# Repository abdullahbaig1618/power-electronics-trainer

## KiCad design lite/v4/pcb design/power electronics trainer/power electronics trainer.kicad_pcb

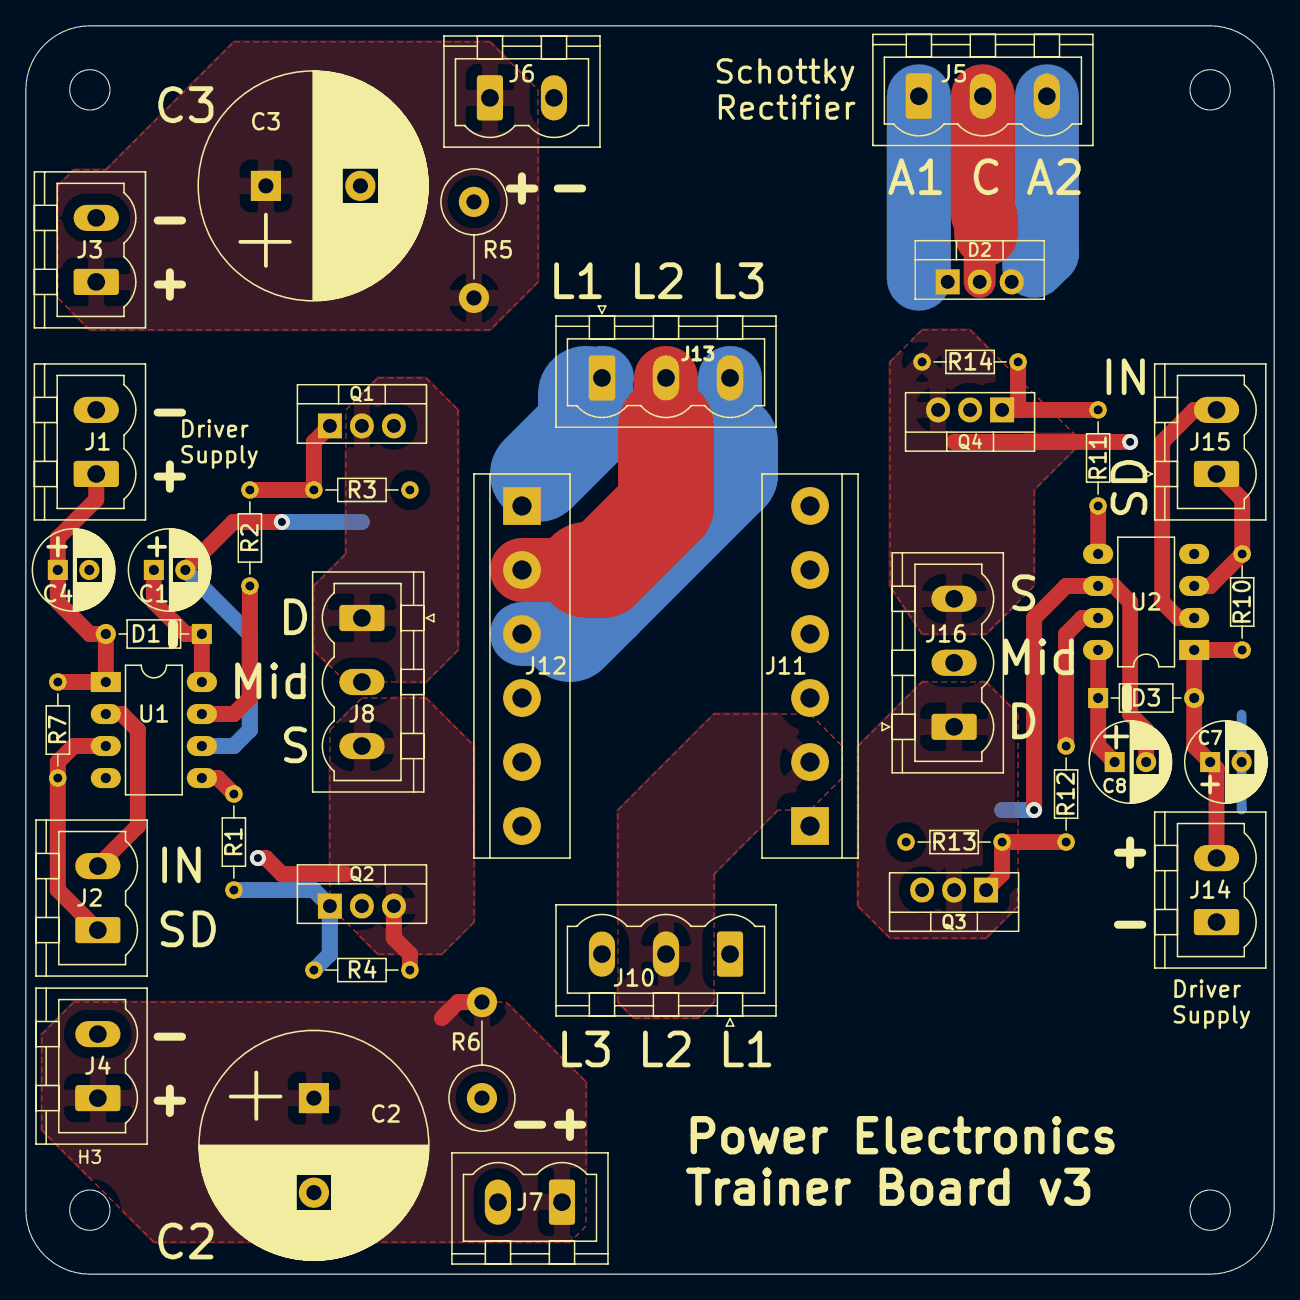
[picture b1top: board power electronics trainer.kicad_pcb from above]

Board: 2 copper layers, 99.1 x 99.1 mm, 46 parts (0 on the bottom side), 35 nets.

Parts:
C1, C4, C7, C8: 10uF; CP_Radial_D6.3mm_P2.50mm
C2, C3: 1000uF; CP_Radial_D18.0mm_P7.50mm
D1, D3: 1N4148; D_DO-35_SOD27_P7.62mm_Horizontal
D2: MBR20100CT; TO-220-3_Vertical
H1, H2, H3, H4: MountingHole; MountingHole_3.2mm_M3
J1, J2, J3, J4, J6, J7, J14, J15: Screw_Terminal_01x02; PhoenixContact_MSTBVA_2,5_2-G-5,08_1x02_P5.08mm_Vertical
J5, J8, J10, J13, J16: Screw_Terminal_01x03; PhoenixContact_MSTBVA_2,5_3-G-5,08_1x03_P5.08mm_Vertical
J11, J12: Conn_01x06_Male; TerminalBlock_bornier-6_P5.08mm
Q1, Q2, Q3, Q4: IRF3205; TO-220-3_Vertical
R1, R2, R11, R12: 27; R_Axial_DIN0204_L3.6mm_D1.6mm_P7.62mm_Horizontal
R3, R4, R7, R10, R13, R14: 10k; R_Axial_DIN0204_L3.6mm_D1.6mm_P7.62mm_Horizontal
R5, R6: 3.3k; R_Axial_DIN0516_L15.5mm_D5.0mm_P7.62mm_Vertical
U1, U2: IR2104; DIP-8_W7.62mm_LongPads

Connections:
C2+: C2.1, J4.1, J7.1, R6.2
C2-: C2.2, J4.2, J7.2, R6.1
C3+: C3.1, J3.1, J6.1, R5.2
C3-: C3.2, J3.2, J6.2, R5.1
unnamed: C1.1, D1.1, U1.8
unnamed: C4.1, D1.2, J1.1, R7.1, U1.1
unnamed: C7.1, D3.2, J14.2, R10.1, U2.1
unnamed: C8.1, D3.1, U2.8
unnamed: D2.1, J5.1
unnamed: D2.2, J5.2
unnamed: D2.3, J5.3
unnamed: J2.1, R7.2, U1.3
unnamed: J2.2, U1.2
unnamed: J10.1, J11.1
unnamed: J10.2, J11.2
unnamed: J10.3, J11.3
unnamed: J12.1, J13.1
unnamed: J12.2, J13.2
unnamed: J12.3, J13.3
unnamed: J15.1, R10.2, U2.3
unnamed: J15.2, U2.2
unnamed: Q1.1, R2.1, R3.2
unnamed: Q2.1, R1.1, R4.2
unnamed: Q3.1, R12.1, R13.2
unnamed: Q4.1, R11.1, R14.2
unnamed: R1.2, U1.5
unnamed: R2.2, U1.7
unnamed: R11.2, U2.5
unnamed: R12.2, U2.7
Q1D: J8.1, Q1.2
Q2S: C4.2, J1.2, J8.3, Q2.3, R4.1, U1.4
Q3D: J16.1, Q3.2
Q4S: C7.2, J14.1, J16.3, Q4.3, R14.1, U2.4
Q12mid: C1.2, J8.2, Q1.3, Q2.2, R3.1, U1.6
Q34mid: C8.2, J16.2, Q3.3, Q4.2, R13.1, U2.6
